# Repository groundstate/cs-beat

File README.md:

# cs-beat
Arduino-controlled LED display of ticking of an atomic clock

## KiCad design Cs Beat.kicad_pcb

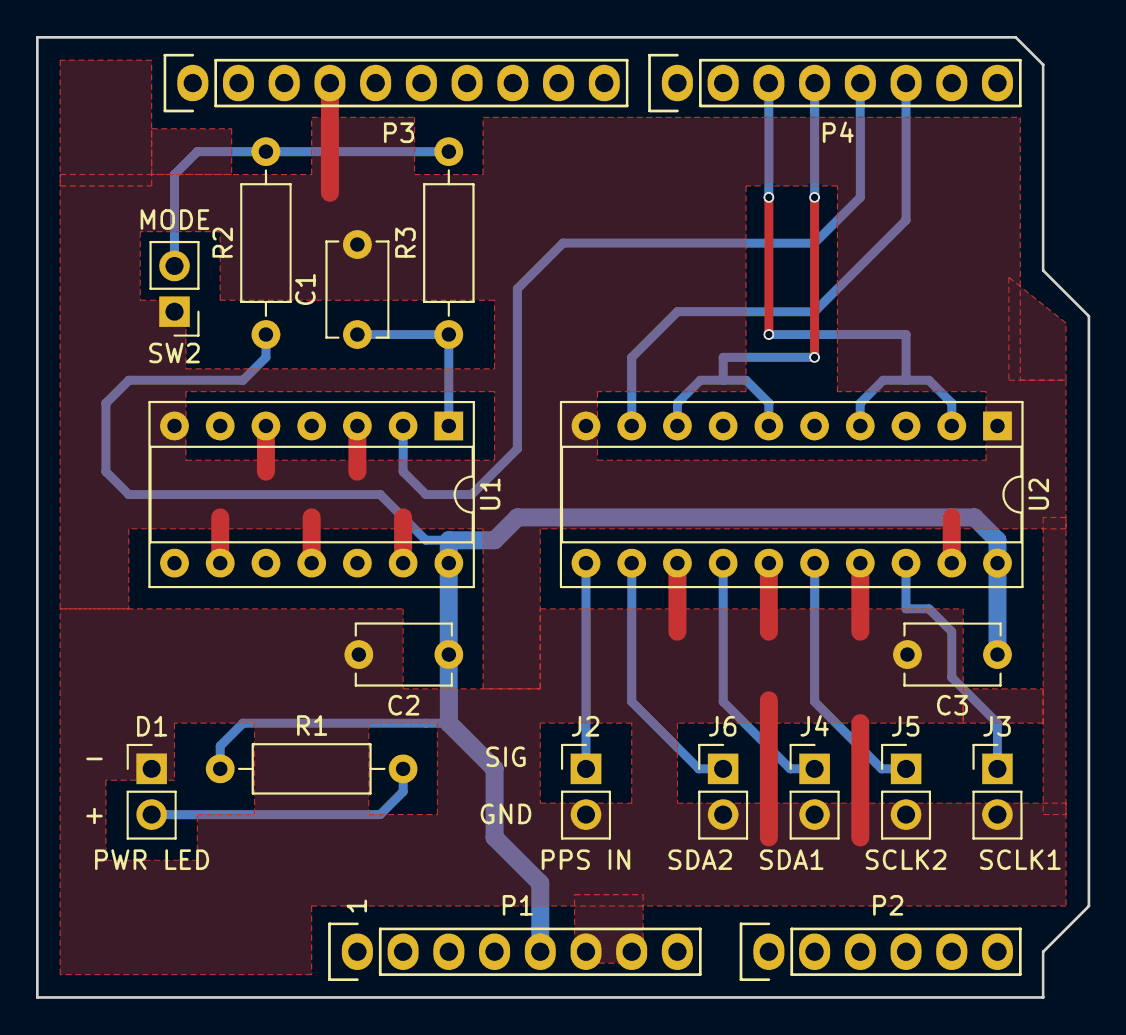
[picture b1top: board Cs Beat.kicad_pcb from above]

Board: 2 copper layers, 58.4 x 53.3 mm, 19 parts (0 on the bottom side), 14 nets.

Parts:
C1, C2, C3: 0.1uF; C_Disc_D5.1mm_W3.2mm_P5.00mm
D1: PWR LED; PinHeader_1x02_P2.54mm_Vertical
J2: PPS IN; PinHeader_1x02_P2.54mm_Vertical
J3: SCLK1; PinHeader_1x02_P2.54mm_Vertical
J4: SDA1; PinHeader_1x02_P2.54mm_Vertical
J5: SCLK2; PinHeader_1x02_P2.54mm_Vertical
J6: SDA2; PinHeader_1x02_P2.54mm_Vertical
P1: Power; Socket_Strip_Arduino_1x08
P2: Analog; Socket_Strip_Arduino_1x06
P3: Digital; Socket_Strip_Arduino_1x10
P4: Digital; Socket_Strip_Arduino_1x08
R1: 470R; R_Axial_DIN0207_L6.3mm_D2.5mm_P10.16mm_Horizontal
R2, R3: 10K; R_Axial_DIN0207_L6.3mm_D2.5mm_P10.16mm_Horizontal
SW2: MODE; PinHeader_1x02_P2.54mm_Vertical
U1: 74HC14; DIP-14_W7.62mm_Socket
U2: 74HC244; DIP-20_W7.62mm_Socket

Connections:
+5V: C2.1, C3.1, P1.5, R1.1, R2.1, U1.14, U2.20
GND: C1.2, C2.2, C3.2, D1.1, J2.2, J3.2, J4.2, J5.2, J6.2, P1.6, P1.7, P3.4, SW2.1, U1.3, U1.5, U1.7, U1.9, U1.11, U1.13, U2.1, U2.10, U2.13, U2.15, U2.17, U2.19
IRQ0: P4.6, U2.9
IRQ1: P4.5, U1.2
unnamed: C1.1, R3.1, U1.1
unnamed: D1.2, R1.2
unnamed: J2.1, U2.11
unnamed: J3.1, U2.18
unnamed: J4.1, U2.14
unnamed: J5.1, U2.16
unnamed: J6.1, U2.12
unnamed: R2.2, R3.2, SW2.2
SCLK: P4.3, U2.2, U2.4
SDA: P4.4, U2.6, U2.8
